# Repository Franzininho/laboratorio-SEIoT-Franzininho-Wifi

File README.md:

## Laboratório de Sistemas Embarcados e IoT - Franzininho Wifi

## O que é este projeto?

O projeto **Laboratório de Sistemas Embarcados e IoT** é um projeto de placa de circuito impresso para facilitar o uso de componentes eletrônicos em oficinas de programação. Este projeto possui um socket para conexão da placa [Franzininho Wifi](https://github.com/Franzininho/Franzininho-WiFi) e diversos periféricos conectados à pinos pré-determinados do socket que podem ser ativados utilizando um conector jumper ou mais.

Esse projeto tem o intuito de auxiliar no ensino de programação utilizando placas microcontroladas já que muitas vezes nas oficinas de programação com placas microcontroladas é despendido muito tempo para lidar com problemas que vem da manipulação do hardware como utilização da protoabord e realização de conexões. Este tempo muitas vezes acaba prejudicando a atividade já que o tempo onde se foca em fazer as conexões eletrônicas poderia ser melhor aproveitado focando na programação realmente.

Sendo assim, utilizando a facilidade de conexão de periféricos da placa é possível reduzir drásticamente o tempo despendido para conexões eletrônicas, focando no objetivo da oficina, que é a programação.

Esse projeto está sob a licença [CERN-OHL-S v2](https://ohwr.org/cern_ohl_s_v2.txt)

## Como ativar os periféricos?

Os periféricos utilizados na placa são ativados através de pinos de ativação. Esses pinos são compostos por dois pinos macho que devem ser conectados. Um desses pinos macho está conectado ao socket da placa e o outro a um pino do componente eletrônico. Dessa forma, o jumper fecha a conexão entre o componente e a placa microcontrolada. Uma exemplo desse tipo de conexão está evidenciado na figura abaixo pelas linhas verdes:

Como "ativador" para os pinos, recomendo o uso do conector da imagem abaixo. Você pode encontrar esse conector como "jumper com aba", "mini jumper com aba", "jumper cap", entre outros.

Além dos pinos de ativação de sinal que conectam o componente ao socket da placa, existem também os pinos de ativação de energia que são responsáveis por energizar o componente.

## Codificação dos pinos de ativação

Devido à quantidade de pinos de ativação usada na placa, foi preciso desenvolver um sistema de codificação para esses pinos. Esse sistema foi idealizado com cada pino sendo representado por dois algarismos. O primeiro indicando a funcionalidade do pino e o segundo indicando uma numeração do pino. As funções dos primeiros algarismos podem ser vistas abaixo:

| Letra |                     Significado                      |
| :---: | :--------------------------------------------------: |
|   0   |                         GND                          |
|   3   |                       VCC 3.3V                       |
|   5   |                        VCC 5V                        |
|   A   |                   Pinos analógicos                   |
|   B   | Pinos conectados em um mesmo pino identificado por A |
|   C   |                      Especiais                       |
|   D   |                    Pinos digitais                    |
|   E   | Pinos conectados em um mesmo pino identificado por D |

O código correspondente a cada pino de ativação foi impresso ao lado desse pino e o mapeamento dos pinos de ativação para os pinos da placa Franzininho Wifi está impresso na placa e também pode ser acessado [clicando aqui](./informacoes/mapeamento.md). Além disso, também foi desenvolvida uma biblioteca para uso em conjunto com a placa que permite o uso dos códigos dos pinos de ativação dentro da programação. [Clique aqui para acessar a **biblioteca laboratorioFW**](https://github.com/Franzininho/biblioteca-laboratorioFW)

A lista dos periféricos disponíveis e dos pinos de ativação necessários para ativar esses periféricos pode ser acessadas [clicando aqui](./informacoes/ativacao-perifericos.md). É importante lembrar que além dos periféricos a placa também conta com conectores para sensores e atuadores externos no formato de pinos macho e de conectores Grove.

## Como o projeto foi desenvolvido?

O projeto foi desenvolvido com o software [KiCad 7](https://www.kicad.org/). Esse software é aberto e está disponível para Linux, MacOS e Windows.

## Adaptadores

Buscando aumentar ainda mais a versatilidade do projeto, estão sendo desenvolvidos adaptadores para a placa que permitem a conexão dela com outras placas microcontroladas.

### Placas adaptadoras desenvolvidas até o momento:

-   [Arduino Uno](https://github.com/Franzininho/laboratorio-SEIoT-adaptador-arduino)

## Certificação OSHWA

[Clique aqui](https://certification.oshwa.org/br000014.html) para acessar
---

#### Feito por [LelePG](https://github.com/LelePG)

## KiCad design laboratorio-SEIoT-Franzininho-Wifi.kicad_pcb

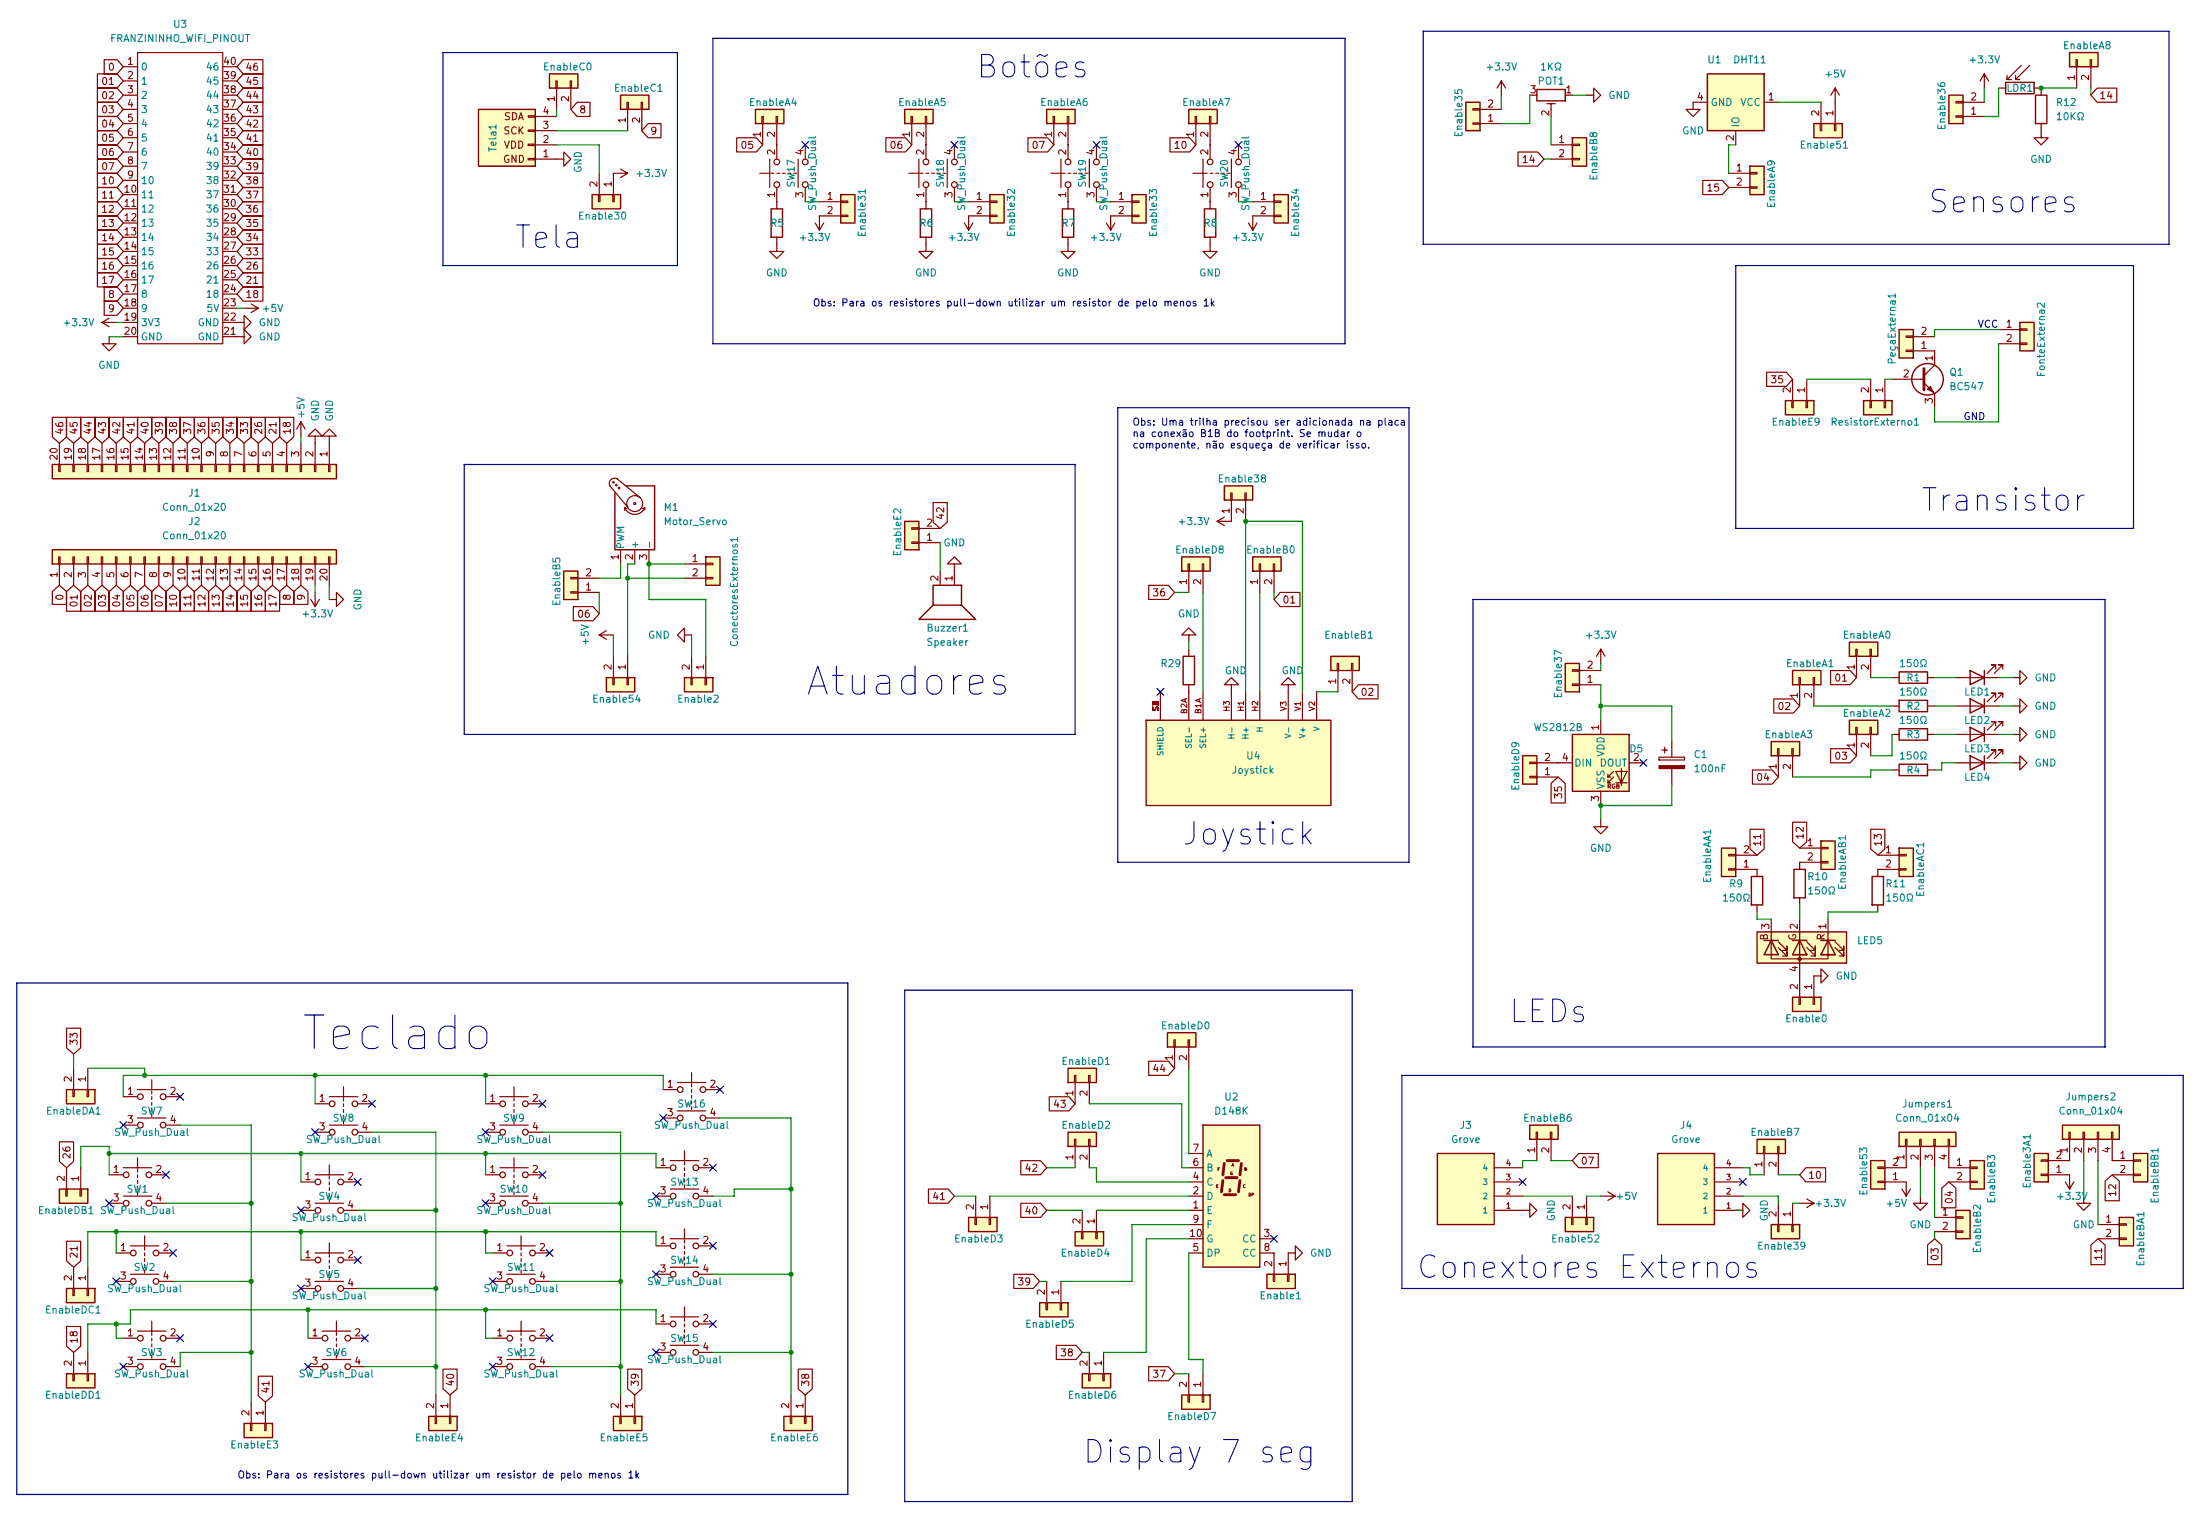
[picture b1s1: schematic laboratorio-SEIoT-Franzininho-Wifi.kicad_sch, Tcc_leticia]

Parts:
Buzzer1: Speaker; Buzzer_12x9.5RM7.6
C1: 100nF; C_0603_1608Metric
ConectoresExternos1: Conn_01x02; PinHeader_1x02_P2.54mm_Vertical
D1: LED1; LED_D5.0mm
D2: LED2; LED_D5.0mm
D3: LED3; LED_D5.0mm
D4: LED4; LED_D5.0mm
D5: WS2812B; LED_WS2812B_PLCC4_5.0x5.0mm_P3.2mm
Enable0, Enable1, Enable2, Enable3A1, Enable30, Enable31, Enable32, Enable33, Enable34, Enable35, Enable36, Enable37, Enable38, Enable39, Enable51, Enable52, Enable53, Enable54: Conn_01x02; PinHeader_1x02_P2.54mm_Vertical
EnableA0, EnableA1, EnableA2, EnableA3, EnableA4, EnableA5, EnableA6, EnableA7, EnableA8, EnableA9: Conn_01x02; PinHeader_1x02_P2.54mm_Vertical
EnableAA1: Conn_01x02; PinHeader_1x02_P2.54mm_Vertical
EnableAB1: Conn_01x02; PinHeader_1x02_P2.54mm_Vertical
EnableAC1: Conn_01x02; PinHeader_1x02_P2.54mm_Vertical
EnableB0, EnableB1, EnableB2, EnableB3, EnableB5, EnableB6, EnableB7, EnableB8: Conn_01x02; PinHeader_1x02_P2.54mm_Vertical
EnableBA1: Conn_01x02; PinHeader_1x02_P2.54mm_Vertical
EnableBB1: Conn_01x02; PinHeader_1x02_P2.54mm_Vertical
EnableC0, EnableC1: Conn_01x02; PinHeader_1x02_P2.54mm_Vertical
EnableD0, EnableD1, EnableD2, EnableD3, EnableD4, EnableD5, EnableD6, EnableD7, EnableD8, EnableD9: Conn_01x02; PinHeader_1x02_P2.54mm_Vertical
EnableDA1: Conn_01x02; PinHeader_1x02_P2.54mm_Vertical
EnableDB1: Conn_01x02; PinHeader_1x02_P2.54mm_Vertical
EnableDC1: Conn_01x02; PinHeader_1x02_P2.54mm_Vertical
EnableDD1: Conn_01x02; PinHeader_1x02_P2.54mm_Vertical
EnableE2, EnableE3, EnableE4, EnableE5, EnableE6, EnableE9: Conn_01x02; PinHeader_1x02_P2.54mm_Vertical
FonteExterna2: Conn_01x02; PinHeader_1x02_P2.54mm_Vertical
J1, J2: Conn_01x20; PinHeader_1x20_P2.54mm_Vertical
J3, J4: Grove; PARTREV A
Jumpers1, Jumpers2: Conn_01x04; PinHeader_1x04_P2.54mm_Vertical
LDR1: LDR07; R_LDR_5.1x4.3mm_P3.4mm_Vertical
LED5: LED_RGBA; LED_D5.0mm-4_RGB
M1: Motor_Servo; PinHeader_1x03_P2.54mm_Vertical
POT1: 1KΩ; Potentiometer_Alps_RK09K_Single_Vertical
PeçaExterna1: Conn_01x02; PinHeader_1x02_P2.54mm_Vertical
Q1: BC547; TO-92_Inline
R1, R2, R3, R4, R9, R10, R11: 150Ω; R_Axial_DIN0204_L3.6mm_D1.6mm_P7.62mm_Horizontal
R5, R6, R7, R8: 150Ω; R_0805_2012Metric
R12: 10KΩ; R_0805_2012Metric
R29: R; R_0805_2012Metric
ResistorExterno1: Conn_01x02; PinSocket_1x02_P2.54mm_Vertical
SW1, SW2, SW3, SW4, SW5, SW6, SW7, SW8, SW9, SW10, SW11, SW12, SW13, SW14, SW15, SW16, SW17, SW18, SW19, SW20: SW_Push_Dual; Switch
Tela1: Conn_01x04; PinHeader_1x04_P2.54mm_Vertical
U1: DHT11; Aosong_DHT11_5.5x12.0_P2.54mm
U2: D148K; D1X8K
U3: FRANZININHO_WIFI_PINOUT
U4: Joystick; PARTREV N/A

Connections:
0: J2.1, U3.1 (0)
01: EnableA0.1, EnableB0.2, J2.2, U3.2 (1)
02: EnableA1.1, EnableB1.2, J2.3, U3.3 (2)
03: EnableA2.1, EnableB2.2, J2.4, U3.4 (3)
04: EnableA3.1, EnableB3.2, J2.5, U3.5 (4)
05: EnableA4.1, J2.6, U3.6 (5)
06: EnableA5.1, EnableB5.1, J2.7, U3.7 (6)
07: EnableA6.1, EnableB6.2, J2.8, U3.8 (7)
8: EnableC0.2, J2.17, U3.17 (8)
9: EnableC1.2, J2.18, U3.18 (9)
10: EnableA7.1, EnableB7.2, J2.9, U3.9 (10)
11: EnableAA1.2, EnableBA1.2, J2.10, U3.10 (11)
12: EnableAB1.1, EnableBB1.2, J2.11, U3.11 (12)
13: EnableAC1.1, J2.12, U3.12 (13)
14: EnableA8.2, EnableB8.2, J2.13, U3.13 (14)
15: EnableA9.2, J2.14, U3.14 (15)
16: J2.15, U3.15 (16)
17: J2.16, U3.16 (17)
18: EnableDD1.2, J1.4, U3.24 (18)
21: EnableDC1.2, J1.5, U3.25 (21)
26: EnableDB1.2, J1.6, U3.26
33: EnableDA1.2, J1.7, U3.27 (33)
34: J1.8, U3.28 (34)
35: EnableD9.1, EnableE9.2, J1.9, U3.29 (35)
36: EnableD8.1, J1.10, U3.30 (36)
37: EnableD7.2, J1.11, U3.31 (37)
38: EnableD6.2, EnableE6.1, J1.12, U3.32 (38)
39: EnableD5.2, EnableE5.1, J1.13, U3.33 (39)
40: EnableD4.2, EnableE4.1, J1.14, U3.34 (40)
41: EnableD3.2, EnableE3.1, J1.15, U3.35 (41)
42: EnableD2.1, EnableE2.2, J1.16, U3.36 (42)
43: EnableD1.1, J1.17, U3.37 (43)
44: EnableD0.1, J1.18, U3.38 (44)
45: J1.19, U3.39 (45)
46: J1.20, U3.40 (46)
+3.3V: Enable3A1.1, Enable30.1, Enable31.2, Enable32.2, Enable33.2, Enable34.2, Enable35.2, Enable36.2, Enable37.2, Enable38.1, Enable39.1, J2.19, U3.19 (3V3)
+5V: Enable51.1, Enable52.1, Enable53.1, Enable54.2, J1.3, U3.23 (5V)
GND: Buzzer1.1, C1.2, D1.1 (K), D2.1 (K), D3.1 (K), D4.1 (K), D5.3 (VSS), Enable0.1, Enable1.1, Enable2.2, J1.1, J1.2, J2.20, J3.1, J4.1, Jumpers1.2, Jumpers2.2, POT1.1, R5.2, R6.2, R7.2, R8.2, R12.2, R29.2, Tela1.1, U1.4 (GND), U3.20 (GND), U3.21 (GND), U3.22 (GND), U4.H3 (H-), U4.V3 (V-)
unnamed: ConectoresExternos1.1, Enable2.1, M1.3 (-)
unnamed: ConectoresExternos1.2, Enable54.1, M1.2 (+)
unnamed: D1.2 (A), R1.2
unnamed: D2.2 (A), R2.1
unnamed: D3.2 (A), R3.2
unnamed: D4.2 (A), R4.2
unnamed: D5.4 (DIN), EnableD9.2
unnamed: C1.1, D5.1 (VDD), Enable37.1
unnamed: Enable0.2, LED5.4 (A)
unnamed: Enable1.2, U2.8 (CC)
unnamed: Enable3A1.2, Jumpers2.1
unnamed: Enable30.2, Tela1.2
unnamed: Enable31.1, SW17.3
unnamed: Enable32.1, SW18.3
unnamed: Enable33.1, SW19.3
unnamed: Enable34.1, SW20.3
unnamed: Enable35.1, POT1.3
unnamed: Enable36.1, LDR1.2
unnamed: Enable38.2, U4.B2B, U4.H1 (H+), U4.V1 (V+)
unnamed: Enable39.2, J4.2
unnamed: Enable51.2, U1.1 (VCC)
unnamed: Enable52.2, J3.2
unnamed: Enable53.2, Jumpers1.1
unnamed: EnableA0.2, R1.1
unnamed: EnableA1.2, R2.2
unnamed: EnableA2.2, R3.1
unnamed: EnableA3.2, R4.1
unnamed: EnableA4.2, SW17.2
unnamed: EnableA5.2, SW18.2
unnamed: EnableA6.2, SW19.2
unnamed: EnableA7.2, SW20.2
unnamed: EnableA8.1, LDR1.1, R12.1
unnamed: EnableA9.1, U1.2 (IO)
unnamed: EnableAA1.1, R9.1
unnamed: EnableAB1.2, R10.1
unnamed: EnableAC1.2, R11.1
unnamed: EnableB0.1, U4.H2 (H)
unnamed: EnableB1.1, U4.V2 (V)
unnamed: EnableB2.1, Jumpers1.3
unnamed: EnableB3.1, Jumpers1.4
unnamed: EnableB5.2, M1.1 (PWM)
unnamed: EnableB6.1, J3.4
unnamed: EnableB7.1, J4.4
unnamed: EnableB8.1, POT1.2
unnamed: EnableBA1.1, Jumpers2.3
unnamed: EnableBB1.1, Jumpers2.4
unnamed: EnableC0.1, Tela1.4
unnamed: EnableC1.1, Tela1.3
unnamed: EnableD0.2, U2.7 (A)
unnamed: EnableD1.2, U2.6 (B)
unnamed: EnableD2.2, U2.4 (C)
unnamed: EnableD3.1, U2.2 (D)
unnamed: EnableD4.1, U2.1 (E)
unnamed: EnableD5.1, U2.9 (F)
unnamed: EnableD6.1, U2.10 (G)
unnamed: EnableD7.1, U2.5 (DP)
unnamed: EnableD8.2, U4.B1A (SEL+)
unnamed: EnableDA1.1, SW7.1, SW8.1, SW9.1, SW16.1
unnamed: EnableDB1.1, SW1.1, SW4.1, SW10.1, SW13.1
unnamed: EnableDC1.1, SW2.1, SW5.1, SW11.1, SW14.1
unnamed: EnableDD1.1, SW3.1, SW6.1, SW12.1, SW15.1
unnamed: Buzzer1.2, EnableE2.1
unnamed: EnableE3.2, SW1.4, SW2.4, SW3.4, SW7.4
unnamed: EnableE4.2, SW4.4, SW5.4, SW6.4, SW8.4
unnamed: EnableE5.2, SW9.4, SW10.4, SW11.4, SW12.4
unnamed: EnableE6.2, SW13.4, SW14.4, SW15.4, SW16.4
unnamed: EnableE9.1, ResistorExterno1.2
unnamed: FonteExterna2.1, PeçaExterna1.2
unnamed: FonteExterna2.2, Q1.3 (E)
unnamed: LED5.3 (BK), R9.2
unnamed: LED5.2 (GK), R10.2
unnamed: LED5.1 (RK), R11.2
unnamed: PeçaExterna1.1, Q1.1 (C)
unnamed: Q1.2 (B), ResistorExterno1.1
unnamed: R5.1, SW17.1
unnamed: R6.1, SW18.1
unnamed: R7.1, SW19.1
unnamed: R8.1, SW20.1
unnamed: R29.1, U4.B2A (SEL-)

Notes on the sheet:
Obs: Para os resistores pull-down utilizar um resistor de pelo menos 1k
Botões
Conextores Externos
GND
Display 7 seg
Obs: Uma trilha precisou ser adicionada na placa na conexão B1B do footprint. Se mudar o componente, não esqueça de verificar isso.
VCC
LEDs
Atuadores
Joystick
Teclado
Transistor
Sensores
Tela

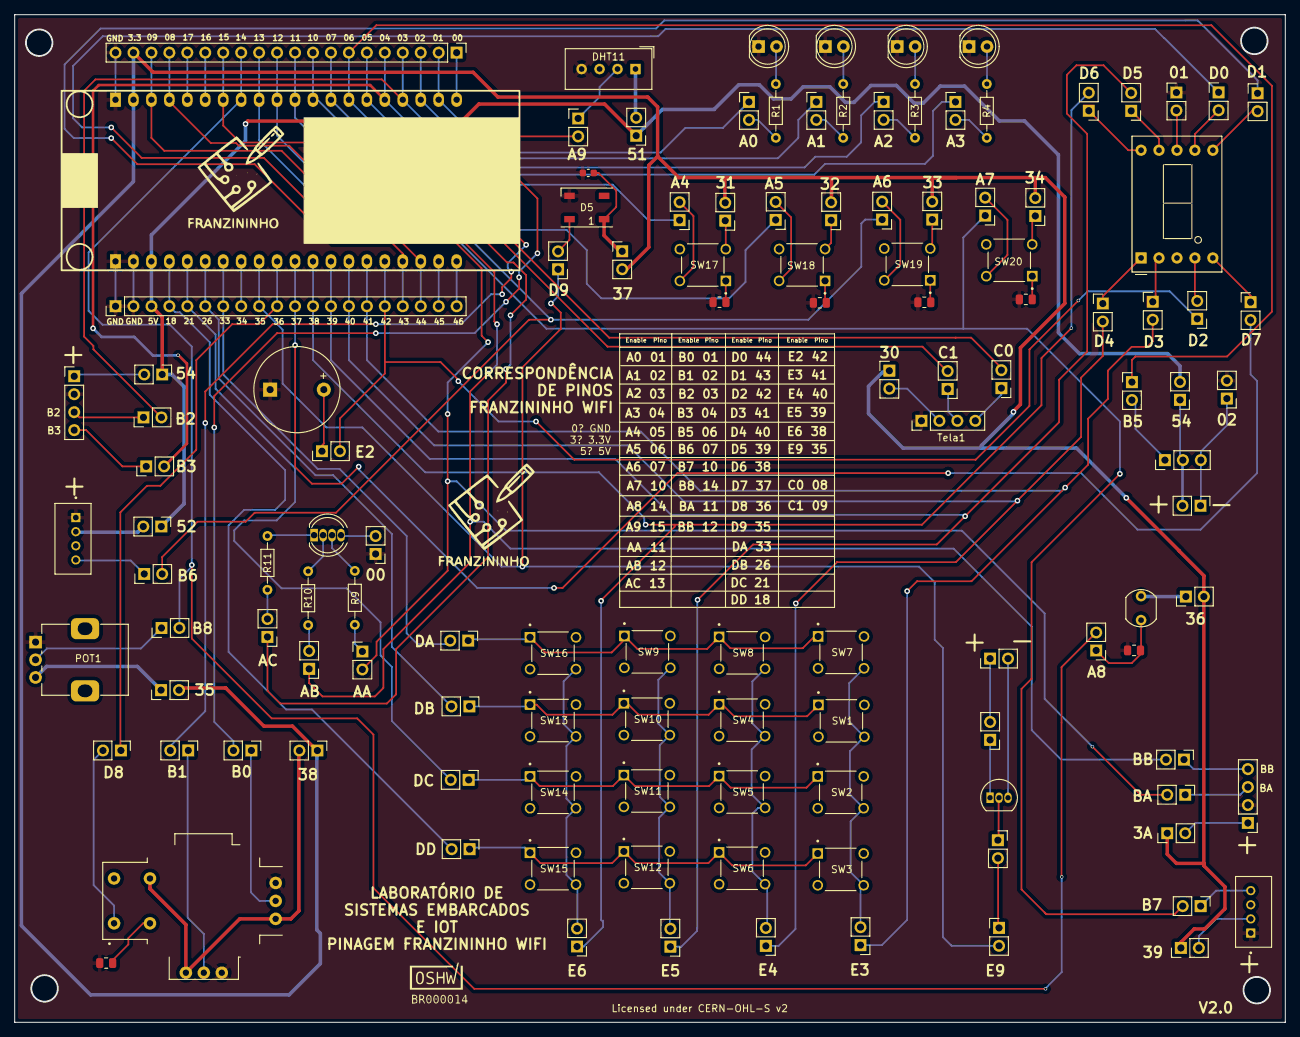
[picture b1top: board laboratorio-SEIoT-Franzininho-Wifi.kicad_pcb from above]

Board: 2 copper layers, 179.8 x 142.6 mm, 124 parts (0 on the bottom side), 117 nets.

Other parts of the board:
G1: LOGO

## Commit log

2023-03-25 commit inicial
2023-03-25 correção dogitignore
2023-03-27 correção de conexão no display de 7 segmentos
2023-05-13 adição da licensa
2023-05-23 certificação adicionada

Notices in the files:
laboratorio-SEIoT-Franzininho-Wifi.kicad_pcb:
Licensed under CERN-OHL-S v2
